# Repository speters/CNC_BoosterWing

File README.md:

# grblHAL BoosterWing

A breakout board for the Texas Instruments EK-TM4C1294XL Launchpad running the [grblHAL TM4C1294](https://github.com/grblHAL/TM4C1294) firmware by [Terje Io](https://github.com/terjeio).

This is a Frankenstein style child of [GRBLHAL2000](https://github.com/Expatria-Technologies/grblhal_2000_PrintNC) and 
[CNC_Boosterpack](https://github.com/terjeio/CNC_Boosterpack).

There were two objectives for this:
  1. follow known-working proven schematics - no questions asked
  2. keep it manufacturable by JLCPCB with the least costs for extended parts

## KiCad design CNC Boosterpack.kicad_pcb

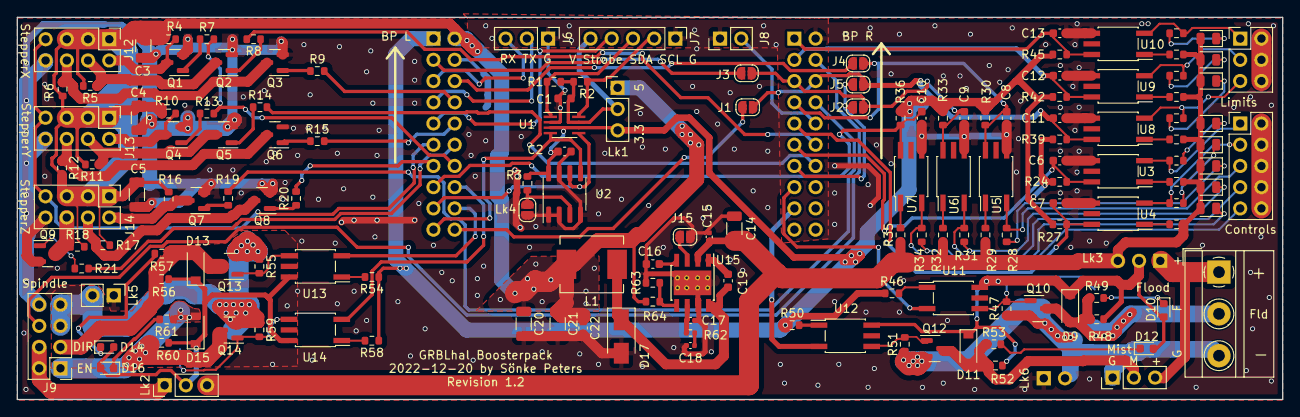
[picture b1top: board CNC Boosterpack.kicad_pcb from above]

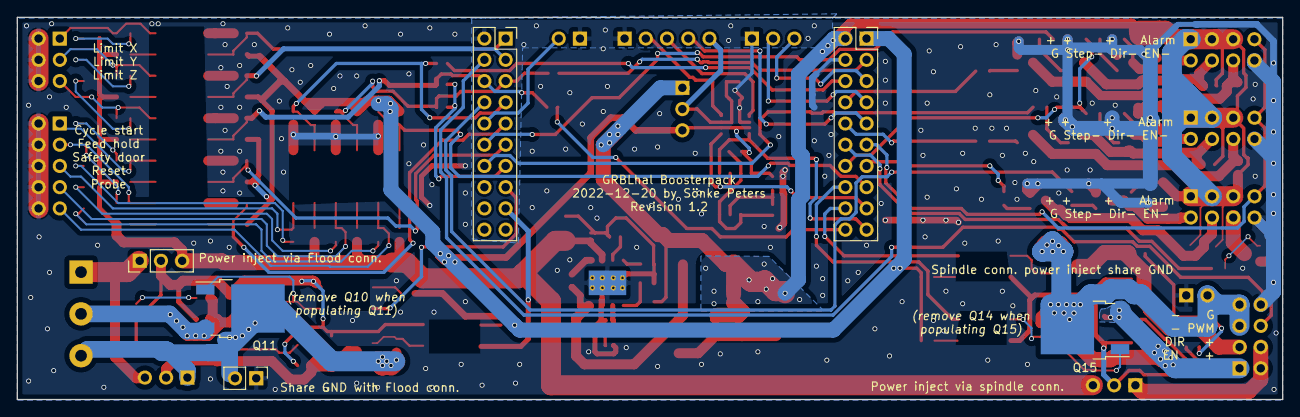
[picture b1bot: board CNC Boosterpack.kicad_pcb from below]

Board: 2 copper layers, 151.4 x 45.7 mm, 159 parts (6 on the bottom side), 111 nets.

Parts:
C1, C2, C6, C7, C8, C9, C10, C11, C12, C13, C19, C22: 100n; C_0603_1608Metric
C3, C4, C5: 22uF 10V; C_1206_3216Metric
C14: 10u; C_1206_3216Metric
C15: 10n; C_0402_1005Metric
C16: 8.2n; C_0603_1608Metric
C17: 10p; C_0402_1005Metric
C18: 6.8n; C_0402_1005Metric
C20, C21: 22u; C_1206_3216Metric
D1, D2, D3, D4, D5, D6, D7, D8: LED y; LED_0805_2012Metric
D9, D11, D13, D15: B5819W SL; D_SOD-123
D10, D12, D14, D16: LED wt; LED_0603_1608Metric
D17: SS54; D_SMA
J1, J2, J3, J4, J5: 0; SolderJumper-2_P1.3mm_Open_RoundedPad1.0x1.5mm
J6: UART/GPIO; PinHeader_1x03_P2.54mm_Vertical
J7: I2C; PinHeader_1x05_P2.54mm_Vertical
J8: RESET; PinHeader_1x02_P2.54mm_Vertical
J9: Spindle; PinHeader_2x04_P2.54mm_Vertical
J10: Mist; PinHeader_1x03_P2.54mm_Vertical
J11: Flood; TerminalBlock_MetzConnect_Type011_RT05503HBWC_1x03_P5.00mm_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
J12, J13, J14: StepperDrv; PinHeader_2x04_P2.54mm_Vertical
J15: 5V off; SolderJumper-2_P1.3mm_Open_RoundedPad1.0x1.5mm
L1: 33uH; L_Neosid_SM-PIC0602H
Lk1: I2CDrv; PinHeader_1x03_P2.54mm_Vertical
Lk2, Lk3: VDrvSel; PinHeader_1x03_P2.54mm_Vertical
Lk4: EEPROMaddr; SolderJumper-2_P1.3mm_Open_RoundedPad1.0x1.5mm
Lk5, Lk6: VDrvGND; PinHeader_1x02_P2.54mm_Vertical
P1: Control; PinHeader_2x05_P2.54mm_Vertical
P2: Limits; PinHeader_2x03_P2.54mm_Vertical
P5: BPConnL; PinSocket_2x10_P2.54mm_Vertical
P6: BPConnR; PinSocket_2x10_P2.54mm_Vertical
Q1, Q2, Q3, Q4, Q5, Q6, Q7, Q8, Q9: MMBT5551; SOT-23
Q10, Q12, Q13, Q14: AO3400A; SOT-23
Q11, Q15: HSU3016; TO-252-2
R1, R2: 6K8; R_0603_1608Metric
R3, R24, R27, R30, R33, R36, R39, R42, R45, R63: 10k; R_0603_1608Metric
R4, R5, R6, R10, R11, R12, R16, R17, R18, R22, R25, R28, R31, R34, R37, R40, R43: 4k7; R_0603_1608Metric
R7, R8, R9, R13, R14, R15, R19, R20, R21, R23, R26, R29, R32, R35, R38, R41, R44: 2k2; R_0603_1608Metric
R46, R50, R54, R58: 510; R_0603_1608Metric
R47, R51, R55, R59: 1k; R_0603_1608Metric
R48, R49, R52, R53, R56, R57, R60, R61: 4,7k; R_0603_1608Metric
R62: 51k; R_0402_1005Metric
R64: 2k; R_0603_1608Metric
U1: TCA9406; SSOP-8_2.95x2.8mm_P0.65mm
U2: M24C64; SOIC-8_3.9x4.9mm_P1.27mm
U3, U4, U5, U6, U7, U8, U9, U10, U11, U12, U13, U14: EL357N(B); SO-5_4.4x3.6mm_P1.27mm_fake
U15: TPS54331DR; TI_SO-PowerPAD-8_ThermalVias

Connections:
+3.3V: C2.1, Lk1.3, P5.1, R3.2, R24.2, R27.2, R30.2, R33.2, R36.2, R39.2, R42.2, R45.2, R46.1, R50.1, R54.1, R58.1, U1.3 (VCCA), U1.6 (OE), U2.8 (VCC)
+12V: C14.1, C15.1, D1.2 (A), D2.2 (A), D3.2 (A), D4.2 (A), D5.2 (A), D6.2 (A), D7.2 (A), D8.2 (A), Lk2.3, Lk3.3, R23.1, R26.1, R29.1, R32.1, R35.1, R38.1, R41.1, R44.1, U15.2 (VIN)
/BPL03: J3.1, P5.3
/BPL06: J4.1, P5.6
/BPL20: J1.1, P5.20
/BPR13: J2.1, J5.1, P6.13
/BP_CS: C6.1, P6.11, R24.1, U3.4
/BP_FH: C7.1, P6.9, R27.1, U4.4
/BP_FLOOD: P6.15, U11.2
/BP_KB_Strobe: J7.4, P5.9
/BP_LimX: C11.1, J1.2, J5.2, P6.6, R39.1, U8.4
/BP_LimY: C12.1, P6.3, R42.1, U9.4
/BP_LimZ: C13.1, P6.1, R45.1, U10.4
/BP_MIST: P6.17, U12.2
/BP_PROBE: C10.1, P5.15, R36.1, U7.4
/BP_Reset: C9.1, J2.2, J3.2, P6.5, R33.1, U6.4
/BP_SCL: P5.17, U1.5 (SCL_A), U2.6 (SCL)
/BP_SD: C8.1, J4.2, P6.7, R30.1, U5.4
/BP_SDA: P5.19, U1.4 (SDA_A), U2.5 (SDA)
/BP_SPINDLE_DIR: P5.18, U13.2
/BP_SPINDLE_EN: P5.16, U14.2
/BP_SPINDLE_PWM: J9.6, P6.4
/CS: P1.1, R22.1, U3.2
/FH: P1.3, R25.1, U4.2
/FLOOD: D9.2 (A), J11.2, Q10.3 (D), Q11.3 (D), R48.1, R49.1
/Flood/GND_MOSFET: J10.1, J11.3, Lk6.2, Q10.2 (S), Q11.2 (S), Q12.2 (S), R47.1, R51.1
/Flood/VCC_MOSFET: D9.1 (K), D10.2 (A), D11.1 (K), D12.2 (A), Lk3.2, R48.2, R52.2, U11.4, U12.4
/LimX: P2.5, R37.1, U8.2
/LimY: P2.3, R40.1, U9.2
/LimZ: P2.1, R43.1, U10.2
/MIST: D11.2 (A), J10.2, Q12.3 (D), R52.1, R53.1
/Probe: P1.9, R34.1, U7.2
/RST: J8.2, P6.10
/Reset: P1.7, R31.1, U6.2
/SD: P1.5, R28.1, U5.2
/SPINDLE_DIR: D13.2 (A), J9.3, Q13.3 (D), R56.1, R57.1
/SPINDLE_EN: D15.2 (A), J9.1, Q14.3 (D), Q15.3 (D), R60.1, R61.1
/STEPPER_ALARM: J12.7, J13.7, J14.7, P5.11
/STEPPER_EN_XY: P5.14, R7.2, R13.2
/STEPPER_EN_Z: P6.8, R19.2
/STEPPER_X_DIR: P6.12, R8.2
/STEPPER_X_STEP: P5.8, R9.2
/STEPPER_Y_DIR: P6.14, R14.2
/STEPPER_Y_STEP: P5.10, R15.2
/STEPPER_Z_DIR: P5.13, R20.2
/STEPPER_Z_STEP: P5.12, R21.2
/Spindle Direction/GND_MOSFET: J9.5, J9.7, Lk5.2, Q13.2 (S), Q14.2 (S), Q15.2 (S), R55.1, R59.1
/Spindle Direction/VCC_MOSFET: D13.1 (K), D14.2 (A), D15.1 (K), D16.2 (A), Lk2.2, R56.2, R60.2, U13.4, U14.4
/Stepper_driverconn X/DIR-: J12.4, Q2.3 (C), R5.1
/Stepper_driverconn X/EN-: J12.2, Q1.3 (C), R4.1
/Stepper_driverconn X/STEP-: J12.6, Q3.3 (C), R6.1
/Stepper_driverconn Y/DIR-: J13.4, Q5.3 (C), R11.1
/Stepper_driverconn Y/EN-: J13.2, Q4.3 (C), R10.1
/Stepper_driverconn Y/STEP-: J13.6, Q6.3 (C), R12.1
/Stepper_driverconn Z/DIR-: J14.4, Q8.3 (C), R17.1
/Stepper_driverconn Z/EN-: J14.2, Q7.3 (C), R16.1
/Stepper_driverconn Z/STEP-: J14.6, Q9.3 (C), R18.1
/UART_RX: J6.3, P5.5
/UART_TX: J6.2, P5.7
/VBUS: C3.1, C4.1, C5.1, C20.1, C21.1, C22.1, J12.1, J12.3, J12.5, J13.1, J13.3, J13.5, J14.1, J14.3, J14.5, L1.2, Lk1.1, P5.2, R4.2, R5.2, R6.2, R10.2, R11.2, R12.2, R16.2, R17.2, R18.2, R63.1
/VCCB: C1.1, J7.5, Lk1.2, R1.1, R2.1, U1.7 (VCCB)
GND: C1.2, C2.2, C3.2, C4.2, C5.2, C6.2, C7.2, C8.2, C9.2, C10.2, C11.2, C12.2, C13.2, C14.2, C15.2, C16.2, C17.2, C18.2, C20.2, C21.2, C22.2, D17.2 (A), J6.1, J7.1, J8.1, J9.8, J12.8, J13.8, J14.8, J15.1, Lk4.1, Lk5.1, Lk6.1, P1.2, P1.4, P1.6, P1.8, P1.10, P2.2, P2.4, P2.6, P5.4, P6.2, Q1.2 (E), Q2.2 (E), Q3.2 (E), Q4.2 (E), Q5.2 (E), Q6.2 (E), Q7.2 (E), Q8.2 (E), Q9.2 (E), R64.2, U1.2 (GND), U2.1 (A0), U2.2 (A1), U2.4 (GND), U2.7 (WP), U3.3, U4.3, U5.3, U6.3, U7.3, U8.3, U9.3, U10.3, U15.7 (GND), U15.9 (PAD)
unnamed: C16.1, U15.4 (SS)
unnamed: C17.1, R62.1, U15.6 (COMP)
unnamed: C18.1, R62.2
unnamed: C19.1, D17.1 (K), L1.1, U15.8 (PH)
unnamed: C19.2, U15.1 (BOOT)
unnamed: D1.1 (K), R22.2
unnamed: D2.1 (K), R25.2
unnamed: D3.1 (K), R28.2
unnamed: D4.1 (K), R31.2
unnamed: D5.1 (K), R34.2
unnamed: D6.1 (K), R37.2
unnamed: D7.1 (K), R40.2
unnamed: D8.1 (K), R43.2
unnamed: D10.1 (K), R49.2
unnamed: D12.1 (K), R53.2
unnamed: D14.1 (K), R57.2
unnamed: D16.1 (K), R61.2
unnamed: J7.2, R2.2, U1.8 (SCL_B)
unnamed: J7.3, R1.2, U1.1 (SDA_B)
unnamed: J9.2, J9.4, Lk2.1
unnamed: J10.3, J11.1, Lk3.1
unnamed: J15.2, U15.3 (EN)
unnamed: Lk4.2, R3.1, U2.3 (A2)
unnamed: Q1.1 (B), R7.1
unnamed: Q2.1 (B), R8.1
unnamed: Q3.1 (B), R9.1
unnamed: Q4.1 (B), R13.1
unnamed: Q5.1 (B), R14.1
unnamed: Q6.1 (B), R15.1
unnamed: Q7.1 (B), R19.1
unnamed: Q8.1 (B), R20.1
unnamed: Q9.1 (B), R21.1
unnamed: Q10.1 (G), Q11.1 (G), R47.2, U11.3
unnamed: Q12.1 (G), R51.2, U12.3
unnamed: Q13.1 (G), R55.2, U13.3
unnamed: Q14.1 (G), Q15.1 (G), R59.2, U14.3
unnamed: R23.2, U3.1
unnamed: R26.2, U4.1
unnamed: R29.2, U5.1
unnamed: R32.2, U6.1
unnamed: R35.2, U7.1
unnamed: R38.2, U8.1
unnamed: R41.2, U9.1
unnamed: R44.2, U10.1
unnamed: R46.2, U11.1
unnamed: R50.2, U12.1
unnamed: R54.2, U13.1
unnamed: R58.2, U14.1
unnamed: R63.2, R64.1, U15.5 (VSENSE)

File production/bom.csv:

Designator,Footprint,Quantity,Value,LCSC Part #
"C1, C10, C11, C12, C13, C19, C2, C22, C6, C7, C8, C9",C_0603_1608Metric,12,100n,C14663
C14,C_1206_3216Metric,1,10u,
C15,C_0402_1005Metric,1,10n,
C16,C_0603_1608Metric,1,8.2n,C27920
C17,C_0402_1005Metric,1,10p,C32949
C18,C_0402_1005Metric,1,6.8n,C1542
"C20, C21",C_1206_3216Metric,2,22u,
"C3, C4, C5",C_1206_3216Metric,3,22uF 10V,C5672
"D1, D2, D3, D4, D5, D6, D7, D8",LED_0805_2012Metric,8,LED y,C2296
"D10, D12, D14, D16",LED_0603_1608Metric,4,LED wt,C2290
"D11, D13, D15, D9",D_SOD-123,4,B5819W SL,C8598
D17,D_SMA,1,SS54,
"J1, J2, J3, J4, J5",SolderJumper-2_P1.3mm_Open_RoundedPad1.0x1.5mm,5,0,
J10,PinHeader_1x03_P2.54mm_Vertical,1,Mist,
J11,TerminalBlock_MetzConnect_Type011_RT05503HBWC_1x03_P5.00mm_Horizontal,1,Flood,
"J12, J13, J14",PinHeader_2x04_P2.54mm_Vertical,3,StepperDrv,
J15,SolderJumper-2_P1.3mm_Open_RoundedPad1.0x1.5mm,1,5V off,
J6,PinHeader_1x03_P2.54mm_Vertical,1,UART/GPIO,
J7,PinHeader_1x05_P2.54mm_Vertical,1,I2C,
J8,PinHeader_1x02_P2.54mm_Vertical,1,RESET,
J9,PinHeader_2x04_P2.54mm_Vertical,1,Spindle,
L1,L_Neosid_SM-PIC0602H,1,33uH,C329385
Lk1,PinHeader_1x03_P2.54mm_Vertical,1,I2CDrv,
"Lk2, Lk3",PinHeader_1x03_P2.54mm_Vertical,2,VDrvSel,
Lk4,SolderJumper-2_P1.3mm_Open_RoundedPad1.0x1.5mm,1,EEPROMaddr,
"Lk5, Lk6",PinHeader_1x02_P2.54mm_Vertical,2,VDrvGND,
P1,PinHeader_2x05_P2.54mm_Vertical,1,Control,
P2,PinHeader_2x03_P2.54mm_Vertical,1,Limits,
P5,PinSocket_2x10_P2.54mm_Vertical,1,BPConnL,
P6,PinSocket_2x10_P2.54mm_Vertical,1,BPConnR,
"Q1, Q2, Q3, Q4, Q5, Q6, Q7, Q8, Q9",SOT-23,9,MMBT5551,C2145
"Q10, Q12, Q13, Q14",SOT-23,4,AO3400A,C20917
"R1, R2",R_0603_1608Metric,2,6K8,C23212
"R10, R11, R12, R16, R17, R18, R22, R25, R28, R31, R34, R37, R4, R40, R43, R5, R6",R_0603_1608Metric,17,4k7,C23162
"R13, R14, R15, R19, R20, R21, R23, R26, R29, R32, R35, R38, R41, R44, R7, R8, R9",R_0603_1608Metric,17,2k2,C4190
"R24, R27, R3, R30, R33, R36, R39, R42, R45, R63",R_0603_1608Metric,10,10k,C25804
"R46, R50, R54, R58",R_0603_1608Metric,4,510,C23193
"R47, R51, R55, R59",R_0603_1608Metric,4,1k,C21190
"R48, R49, R52, R53, R56, R57, R60, R61",R_0603_1608Metric,8,"4,7k",C23162
R62,R_0402_1005Metric,1,51k,C25794
R64,R_0603_1608Metric,1,2k,C22975
U1,SSOP-8_2.95x2.8mm_P0.65mm,1,TCA9406,C337496
"U10, U11, U12, U13, U14, U3, U4, U5, U6, U7, U8, U9",SO-5_4.4x3.6mm_P1.27mm_fake,12,EL357N(B),C6649
U15,TI_SO-PowerPAD-8_ThermalVias,1,TPS54331DR,C9865
U2,SOIC-8_3.9x4.9mm_P1.27mm,1,M24C64,C79988

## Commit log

2022-11-24 some part rotations, JLCPCB ordered #W202211241441380
2024-01-31 added JLCPCB production files
2024-01-31 schem page 1 as PNG

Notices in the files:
CNC Boosterpack.kicad_pcb:
Licensed under CERN OHL v.1.2 or later
